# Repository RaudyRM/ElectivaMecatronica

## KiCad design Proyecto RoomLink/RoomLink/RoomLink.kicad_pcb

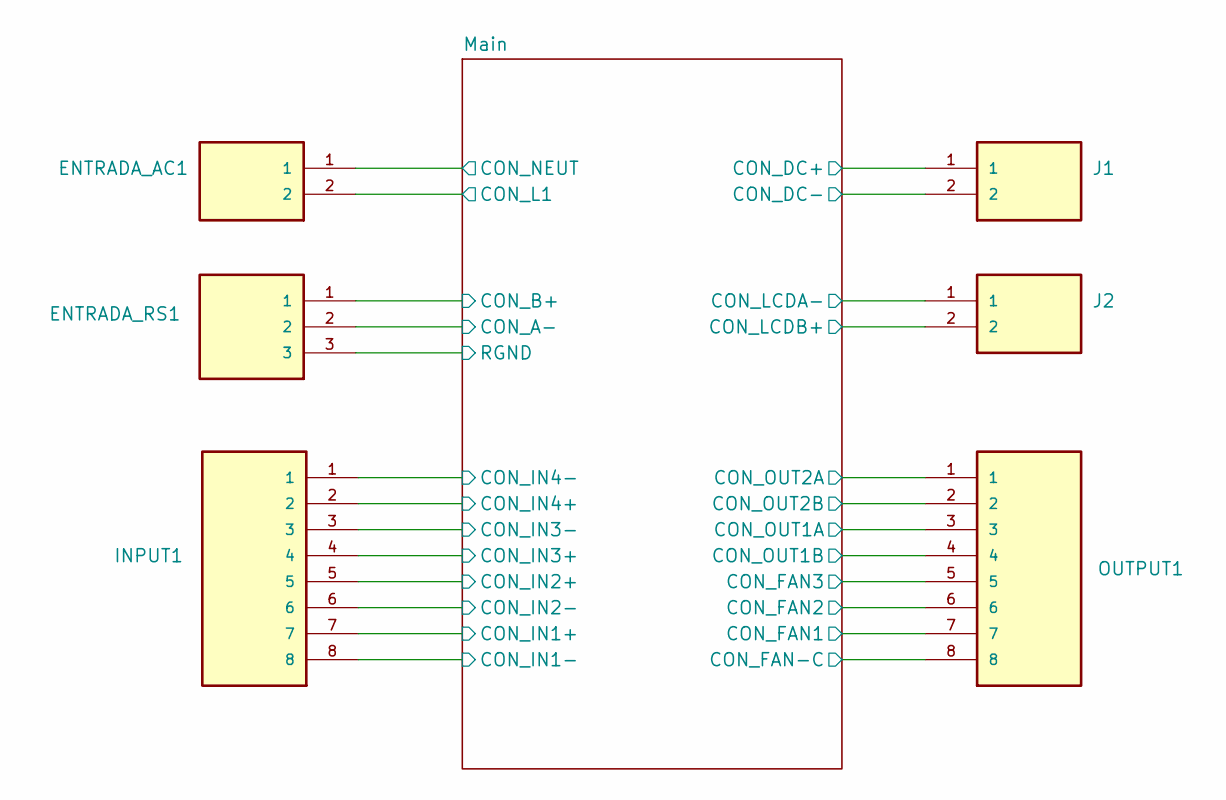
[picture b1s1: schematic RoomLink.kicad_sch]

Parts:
ENTRADA_AC1: TBP03R1-350-02BE; CUI_TBP03R1-350-02BE; PARTREV 1.0
ENTRADA_RS1: TBP03R1-350-03BE; CUI_TBP03R1-350-03BE; PARTREV 1.0
INPUT1: TBP03R1-350-08BE; CUI_TBP03R1-350-08BE; PARTREV 1.0
J1, J2: TBP03R1-350-02BE; CUI_TBP03R1-350-02BE; PARTREV 1.0
OUTPUT1: TBP03R1-350-08BE; CUI_TBP03R1-350-08BE; PARTREV 1.0

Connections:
+12V: J1.1; also elsewhere on the board
/Main/CON_A-: ENTRADA_RS1.2; also elsewhere on the board
/Main/CON_B+: ENTRADA_RS1.1; also elsewhere on the board
/Main/CON_FAN1: OUTPUT1.7; also elsewhere on the board
/Main/CON_FAN2: OUTPUT1.6; also elsewhere on the board
/Main/CON_FAN3: OUTPUT1.5; also elsewhere on the board
/Main/CON_FAN-C: OUTPUT1.8; also elsewhere on the board
/Main/CON_IN1+: INPUT1.7; also elsewhere on the board
/Main/CON_IN1-: INPUT1.8; also elsewhere on the board
/Main/CON_IN2+: INPUT1.5; also elsewhere on the board
/Main/CON_IN2-: INPUT1.6; also elsewhere on the board
/Main/CON_IN3+: INPUT1.4; also elsewhere on the board
/Main/CON_IN3-: INPUT1.3; also elsewhere on the board
/Main/CON_IN4+: INPUT1.2; also elsewhere on the board
/Main/CON_IN4-: INPUT1.1; also elsewhere on the board
/Main/CON_L1: ENTRADA_AC1.2; also elsewhere on the board
/Main/CON_LCDA-: J2.1; also elsewhere on the board
/Main/CON_LCDB+: J2.2; also elsewhere on the board
/Main/CON_NEUT: ENTRADA_AC1.1; also elsewhere on the board
/Main/CON_OUT1A: OUTPUT1.3; also elsewhere on the board
/Main/CON_OUT1B: OUTPUT1.4; also elsewhere on the board
/Main/CON_OUT2A: OUTPUT1.1; also elsewhere on the board
/Main/CON_OUT2B: OUTPUT1.2; also elsewhere on the board
/Main/RGND: ENTRADA_RS1.3; also elsewhere on the board
Earth: J1.2; also elsewhere on the board

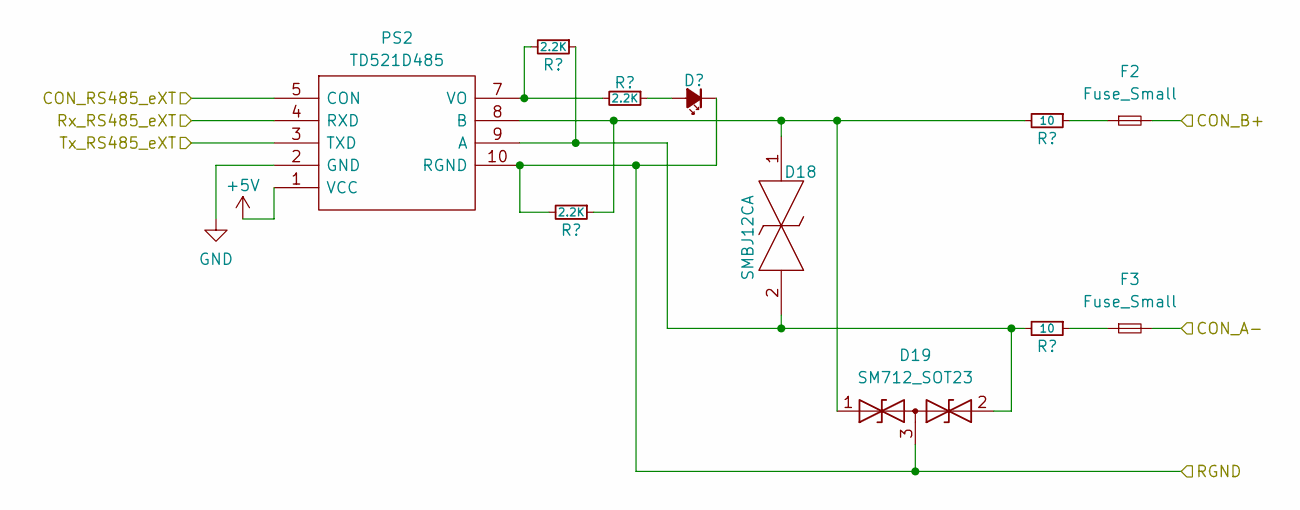
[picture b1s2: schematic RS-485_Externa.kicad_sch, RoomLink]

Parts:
D17: LED_Small_Filled; LED_0805_2012Metric_Pad1.15x1.40mm_HandSolder
D18: SMBJ12CA; DIONM5436X261N; Mouser Part Number 576-SMBJ12CA
D19: SM712_SOT23; SOT-23
F2, F3: Fuse_Small; PTS120660V010
PS2: TD521D485; Manufacturer_Part_Number TD521D485
R36, R37, R38: 2.2K; R_0805_2012Metric_Pad1.20x1.40mm_HandSolder
R39, R40: 10; R_0805_2012Metric_Pad1.20x1.40mm_HandSolder

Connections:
+5V: PS2.1 (VCC)
/Main/CON_A-: F3.2; also elsewhere on the board
/Main/CON_B+: F2.2; also elsewhere on the board
/Main/Control/CON_RS485_eXT: PS2.5 (CON); also elsewhere on the board
/Main/Control/Rx_RS485_eXT: PS2.4 (RXD); also elsewhere on the board
/Main/Control/Tx_RS485_eXT: PS2.3 (TXD); also elsewhere on the board
/Main/RGND: D17.1 (K), D19.3 (common), PS2.10 (RGND), R37.2; also elsewhere on the board
GND: PS2.2 (GND); also elsewhere on the board
unnamed: D17.2 (A), R38.1
unnamed: D18.1, D19.1 (A1), PS2.8 (B), R37.1, R39.2
unnamed: D18.2, D19.2 (A2), PS2.9 (A), R36.1, R40.2
unnamed: F2.1, R39.1
unnamed: F3.1, R40.1
unnamed: PS2.7 (VO), R36.2, R38.2

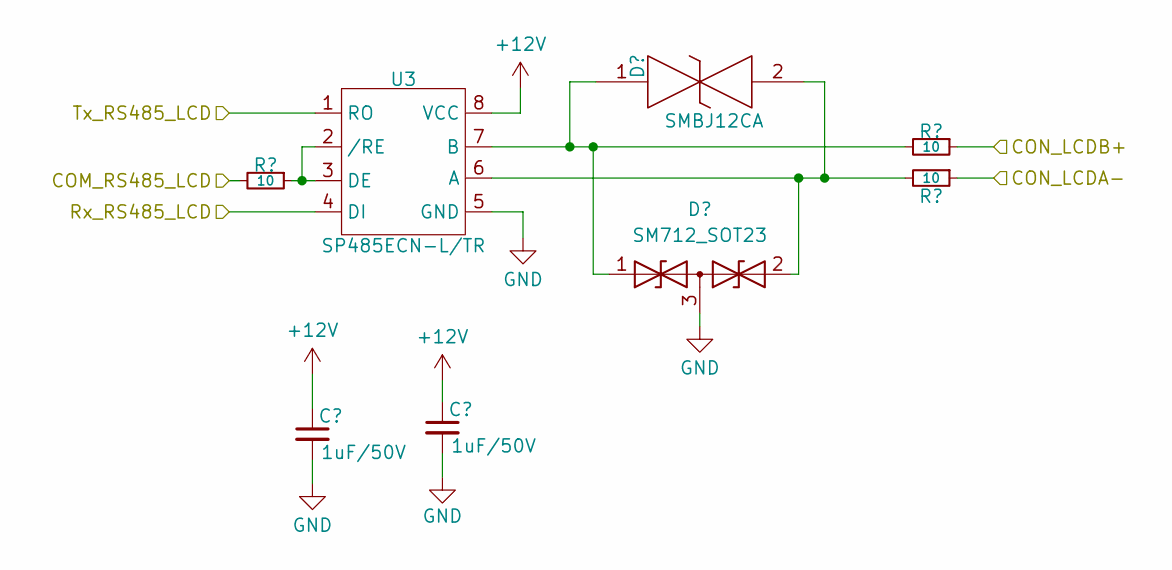
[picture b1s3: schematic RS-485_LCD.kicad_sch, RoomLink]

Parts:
C4, C5: 1uF/50V; C_0805_2012Metric; PartNo C0805C104K5RAC7411
D2: SMBJ12CA; DIONM5436X261N; Mouser Part Number 576-SMBJ12CA
D3: SM712_SOT23; SOT-23
R8, R9, R10: 10; R_0805_2012Metric_Pad1.20x1.40mm_HandSolder
U3: SP485ECN-L/TR; SP485ECN-LTR

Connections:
+12V: C4.1, C5.1, U3.8 (VCC); also elsewhere on the board
/Main/CON_LCDA-: R10.1; also elsewhere on the board
/Main/CON_LCDB+: R9.1; also elsewhere on the board
/Main/Control/COM_RS485_LCD: R8.2; also elsewhere on the board
/Main/Control/Rx_RS485_LCD: U3.4 (DI); also elsewhere on the board
/Main/Control/Tx_RS485_LCD: U3.1 (RO); also elsewhere on the board
GND: C4.2, C5.2, D3.3 (common), U3.5 (GND); also elsewhere on the board
unnamed: D2.1, D3.1 (A1), R9.2, U3.7 (B)
unnamed: D2.2, D3.2 (A2), R10.2, U3.6 (A)
unnamed: R8.1, U3.2 (/RE), U3.3 (DE)

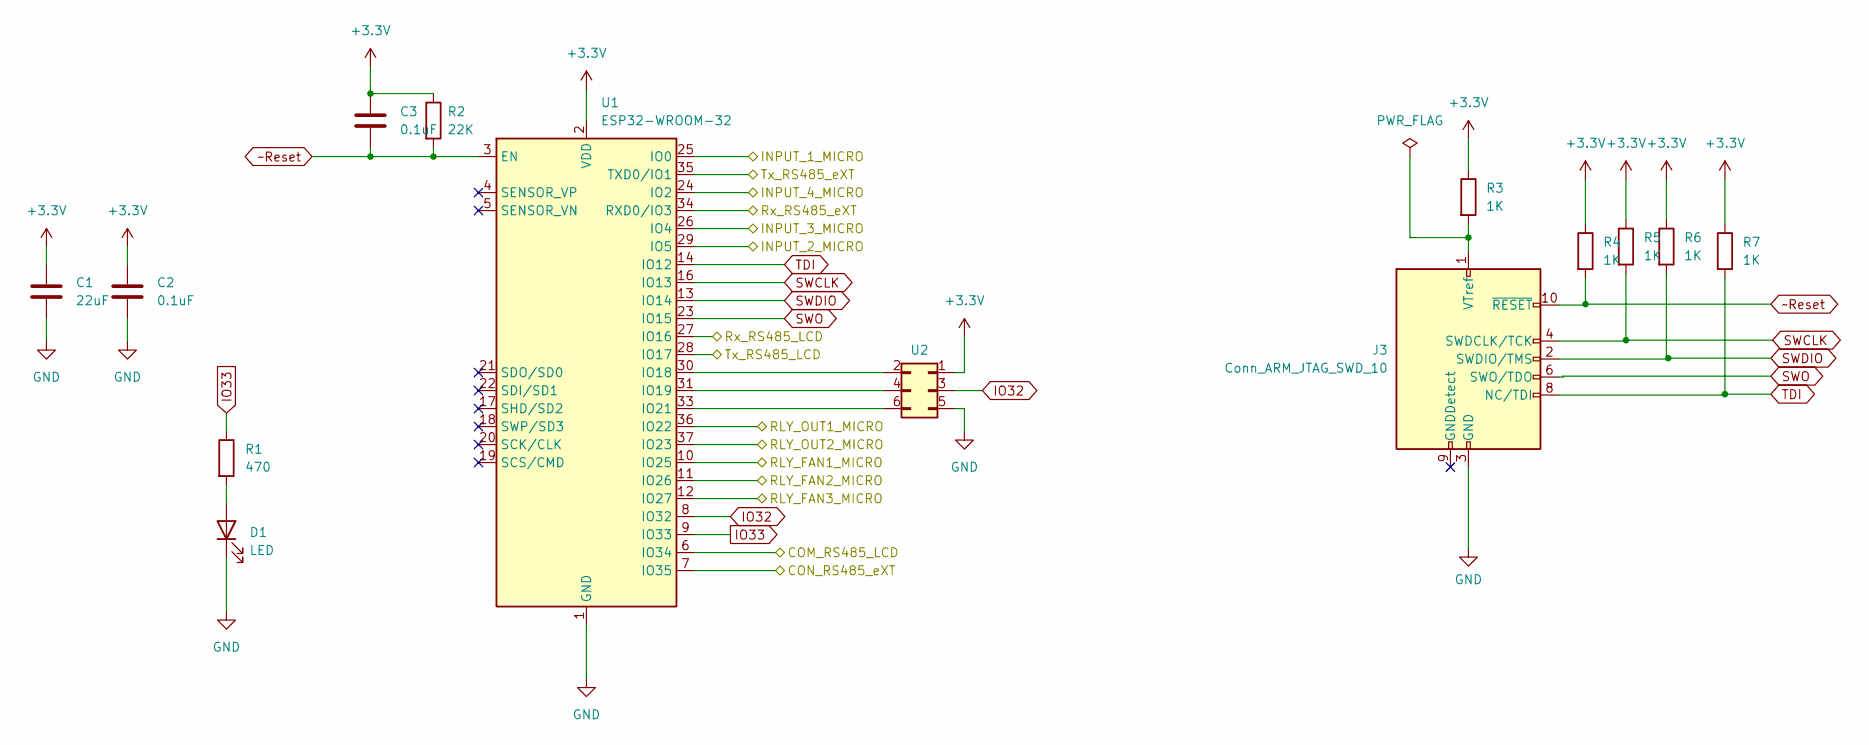
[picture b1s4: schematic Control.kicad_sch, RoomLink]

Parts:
C1: 22uF; C_0805_2012Metric
C2, C3: 0.1uF; C_0805_2012Metric
D1: LED; LED_0805_2012Metric
J3: Conn_ARM_JTAG_SWD_10; PinHeader_2x05_P1.27mm_Vertical
R1: 470; R_0805_2012Metric
R2: 22K; R_0805_2012Metric
R3, R4, R5, R6, R7: 1K; R_0805_2012Metric
U1: ESP32-WROOM-32; ESP32WROOM32EN4
U2: PinHeader2x3

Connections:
+3.3V: C1.1, C2.1, C3.1, R2.1, R3.1, R4.1, R5.1, R6.1, R7.1, U1.2 (VDD), U2.1; also elsewhere on the board
/Main/Control/COM_RS485_LCD: U1.6 (IO34); also elsewhere on the board
/Main/Control/CON_RS485_eXT: U1.7 (IO35); also elsewhere on the board
/Main/Control/INPUT_1_MICRO: U1.25 (IO0); also elsewhere on the board
/Main/Control/INPUT_2_MICRO: U1.29 (IO5); also elsewhere on the board
/Main/Control/INPUT_3_MICRO: U1.26 (IO4); also elsewhere on the board
/Main/Control/INPUT_4_MICRO: U1.24 (IO2); also elsewhere on the board
/Main/Control/RLY_FAN1_MICRO: U1.10 (IO25); also elsewhere on the board
/Main/Control/RLY_FAN2_MICRO: U1.11 (IO26); also elsewhere on the board
/Main/Control/RLY_FAN3_MICRO: U1.12 (IO27); also elsewhere on the board
/Main/Control/RLY_OUT1_MICRO: U1.36 (IO22); also elsewhere on the board
/Main/Control/RLY_OUT2_MICRO: U1.37 (IO23); also elsewhere on the board
/Main/Control/Rx_RS485_LCD: U1.27 (IO16); also elsewhere on the board
/Main/Control/Rx_RS485_eXT: U1.34 (RXD0/IO3); also elsewhere on the board
/Main/Control/Tx_RS485_LCD: U1.28 (IO17); also elsewhere on the board
/Main/Control/Tx_RS485_eXT: U1.35 (TXD0/IO1); also elsewhere on the board
GND: C1.2, C2.2, D1.1 (K), J3.3 (GND), J3.5 (GND), U1.1 (GND), U1.15 (GND), U1.38 (GND), U1.39 (GND), U2.5; also elsewhere on the board
IO32: U1.8 (IO32), U2.3
IO33: R1.1, U1.9 (IO33)
unnamed: D1.2 (A), R1.2
unnamed: J3.1 (VTref), R3.2
unnamed: U1.30 (IO18), U2.2
unnamed: U1.31 (IO19), U2.4
unnamed: U1.33 (IO21), U2.6
SWCLK: J3.4 (SWDCLK/TCK), R5.2, U1.16 (IO13)
SWDIO: J3.2 (SWDIO/TMS), R6.2, U1.13 (IO14)
SWO: J3.6 (SWO/TDO), U1.23 (IO15)
TDI: J3.8 (NC/TDI), R7.2, U1.14 (IO12)
~Reset: C3.2, J3.10 (~RESET), R2.2, R4.2, U1.3 (EN)

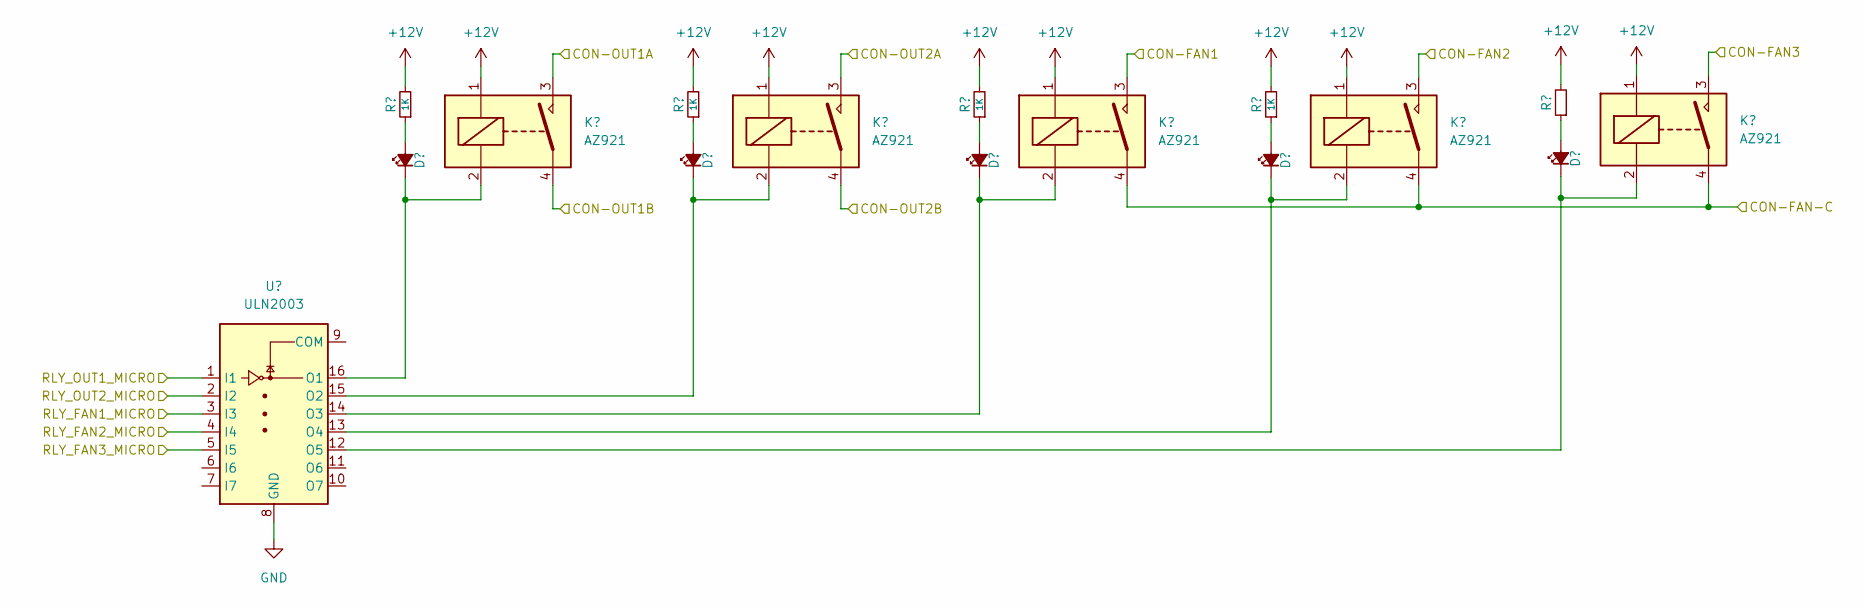
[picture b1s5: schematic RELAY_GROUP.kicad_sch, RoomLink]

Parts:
D4, D5, D6, D7, D8: LED_Small_Filled; LED_0805_2012Metric_Pad1.15x1.40mm_HandSolder
K1, K2, K3, K4, K5: AZ921
R11, R12, R13, R14, R15: 1K; R_0805_2012Metric_Pad1.20x1.40mm_HandSolder
U4: ULN2003; ULN2003-16N

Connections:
+12V: K1.1, K2.1, K3.1, K4.1, K5.1, R11.2, R12.2, R13.2, R14.2, R15.2; also elsewhere on the board
/Main/CON_FAN1: K3.3; also elsewhere on the board
/Main/CON_FAN2: K4.3; also elsewhere on the board
/Main/CON_FAN3: K5.3; also elsewhere on the board
/Main/CON_FAN-C: K3.4, K4.4, K5.4; also elsewhere on the board
/Main/CON_OUT1A: K1.3; also elsewhere on the board
/Main/CON_OUT1B: K1.4; also elsewhere on the board
/Main/CON_OUT2A: K2.3; also elsewhere on the board
/Main/CON_OUT2B: K2.4; also elsewhere on the board
/Main/Control/RLY_FAN1_MICRO: U4.3 (I3); also elsewhere on the board
/Main/Control/RLY_FAN2_MICRO: U4.4 (I4); also elsewhere on the board
/Main/Control/RLY_FAN3_MICRO: U4.5 (I5); also elsewhere on the board
/Main/Control/RLY_OUT1_MICRO: U4.1 (I1); also elsewhere on the board
/Main/Control/RLY_OUT2_MICRO: U4.2 (I2); also elsewhere on the board
GND: U4.8 (GND); also elsewhere on the board
unnamed: D4.2 (A), R11.1
unnamed: D4.1 (K), K1.2, U4.16 (O1)
unnamed: D5.2 (A), R12.1
unnamed: D5.1 (K), K2.2, U4.15 (O2)
unnamed: D6.2 (A), R13.1
unnamed: D6.1 (K), K3.2, U4.14 (O3)
unnamed: D7.2 (A), R14.1
unnamed: D7.1 (K), K4.2, U4.13 (O4)
unnamed: D8.2 (A), R15.1
unnamed: D8.1 (K), K5.2, U4.12 (O5)

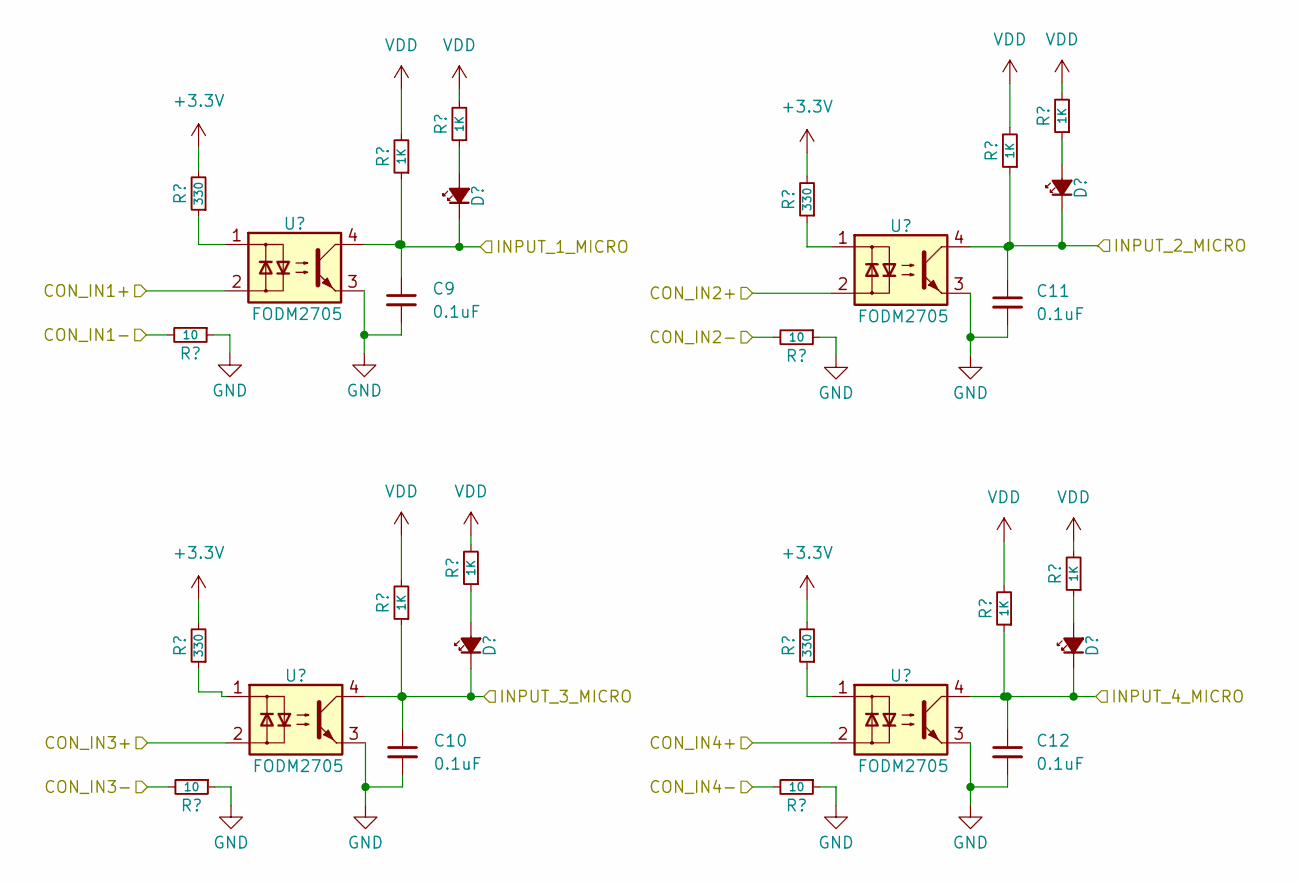
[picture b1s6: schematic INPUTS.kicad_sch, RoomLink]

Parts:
C9, C10, C11, C12: 0.1uF; C_0805_2012Metric; PartNo C0805C104K5RAC7411
D13, D14, D15, D16: LED_Small_Filled; LED_0805_2012Metric_Pad1.15x1.40mm_HandSolder
R20, R21, R28, R29: 10; R_0805_2012Metric_Pad1.20x1.40mm_HandSolder
R22, R23, R30, R31: 330; R_0805_2012Metric_Pad1.20x1.40mm_HandSolder
R24, R25, R26, R27, R32, R33, R34, R35: 1K; R_0805_2012Metric_Pad1.20x1.40mm_HandSolder
U6, U7, U8, U9: FODM2705; FODM2705-4N

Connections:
+3.3V: R22.2, R23.2, R30.2, R31.2; also elsewhere on the board
/Main/CON_IN1+: U6.2; also elsewhere on the board
/Main/CON_IN1-: R20.2; also elsewhere on the board
/Main/CON_IN2+: U8.2; also elsewhere on the board
/Main/CON_IN2-: R28.2; also elsewhere on the board
/Main/CON_IN3+: U7.2; also elsewhere on the board
/Main/CON_IN3-: R21.2; also elsewhere on the board
/Main/CON_IN4+: U9.2; also elsewhere on the board
/Main/CON_IN4-: R29.2; also elsewhere on the board
/Main/Control/INPUT_1_MICRO: C9.1, D13.1 (K), R24.1, U6.4; also elsewhere on the board
/Main/Control/INPUT_2_MICRO: C11.1, D15.1 (K), R33.1, U8.4; also elsewhere on the board
/Main/Control/INPUT_3_MICRO: C10.1, D14.1 (K), R25.1, U7.4; also elsewhere on the board
/Main/Control/INPUT_4_MICRO: C12.1, D16.1 (K), R32.1, U9.4; also elsewhere on the board
GND: C9.2, C10.2, C11.2, C12.2, R20.1, R21.1, R28.1, R29.1, U6.3, U7.3, U8.3, U9.3; also elsewhere on the board
unnamed: D13.2 (A), R26.1
unnamed: D14.2 (A), R27.1
unnamed: D15.2 (A), R34.1
unnamed: D16.2 (A), R35.1
unnamed: R22.1, U6.1
unnamed: R23.1, U7.1
unnamed: R30.1, U8.1
unnamed: R31.1, U9.1
VDD: R24.2, R25.2, R26.2, R27.2, R32.2, R33.2, R34.2, R35.2; also elsewhere on the board

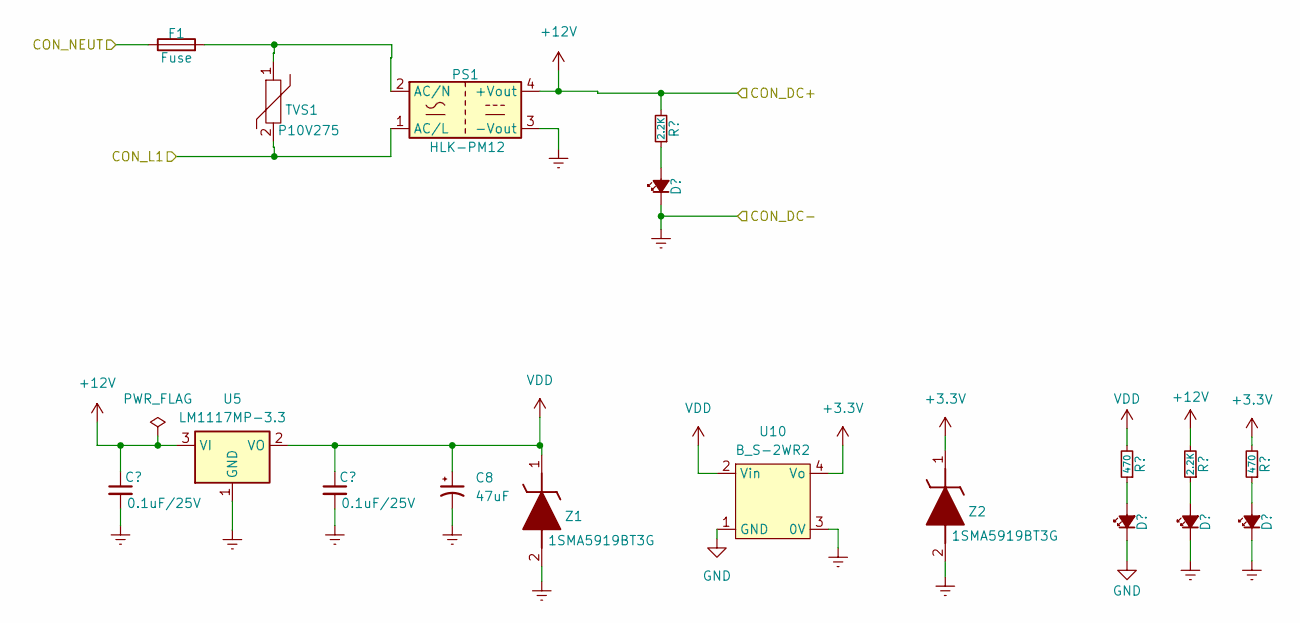
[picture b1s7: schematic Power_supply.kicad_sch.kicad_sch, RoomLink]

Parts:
C6, C7: 0.1uF/25V; C_0805_2012Metric; PartNo C0805C104K5RAC7411
C8: 47uF; CP_Elec_5x5.4
D9, D10, D11, D12: LED_Small_Filled; LED_0805_2012Metric_Pad1.15x1.40mm_HandSolder
F1: Fuse; fuse20x5
PS1: HLK-PM12; Converter_ACDC_HiLink_HLK-PMxx
R16, R18: 2.2K; R_0805_2012Metric_Pad1.20x1.40mm_HandSolder
R17, R19: 470; R_0805_2012Metric_Pad1.20x1.40mm_HandSolder
TVS1: P10V275; RV_Disc_D12mm_W6.7mm_P7.5mm
U5: LM1117MP-3.3; SOT-223-3_TabPin2
U10: B_S-2WR2
Z1, Z2: 1SMA5919BT3G; DIONM5436X261N; Mouser Part Number 863-1SMA5919BT3G

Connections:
+3.3V: R19.2, U10.4 (Vo), Z2.1 (K); also elsewhere on the board
+12V: C6.1, PS1.4 (+Vout), R16.2, R18.2, U5.3 (VI); also elsewhere on the board
/Main/CON_L1: PS1.1 (AC/L), TVS1.2; also elsewhere on the board
/Main/CON_NEUT: F1.1; also elsewhere on the board
Earth: C6.2, C7.2, C8.2, D9.1 (K), D11.1 (K), D12.1 (K), PS1.3 (-Vout), U5.1 (GND), U10.3 (0V), Z1.2 (A), Z2.2 (A); also elsewhere on the board
GND: D10.1 (K), U10.1 (GND); also elsewhere on the board
unnamed: D9.2 (A), R16.1
unnamed: D10.2 (A), R17.1
unnamed: D11.2 (A), R18.1
unnamed: D12.2 (A), R19.1
unnamed: F1.2, PS1.2 (AC/N), TVS1.1
VDD: C7.1, C8.1, R17.2, U5.2 (VO), U10.2 (Vin), Z1.1 (K); also elsewhere on the board

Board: 2 copper layers, 101 parts (0 on the bottom side), 87 nets, no tracks yet.

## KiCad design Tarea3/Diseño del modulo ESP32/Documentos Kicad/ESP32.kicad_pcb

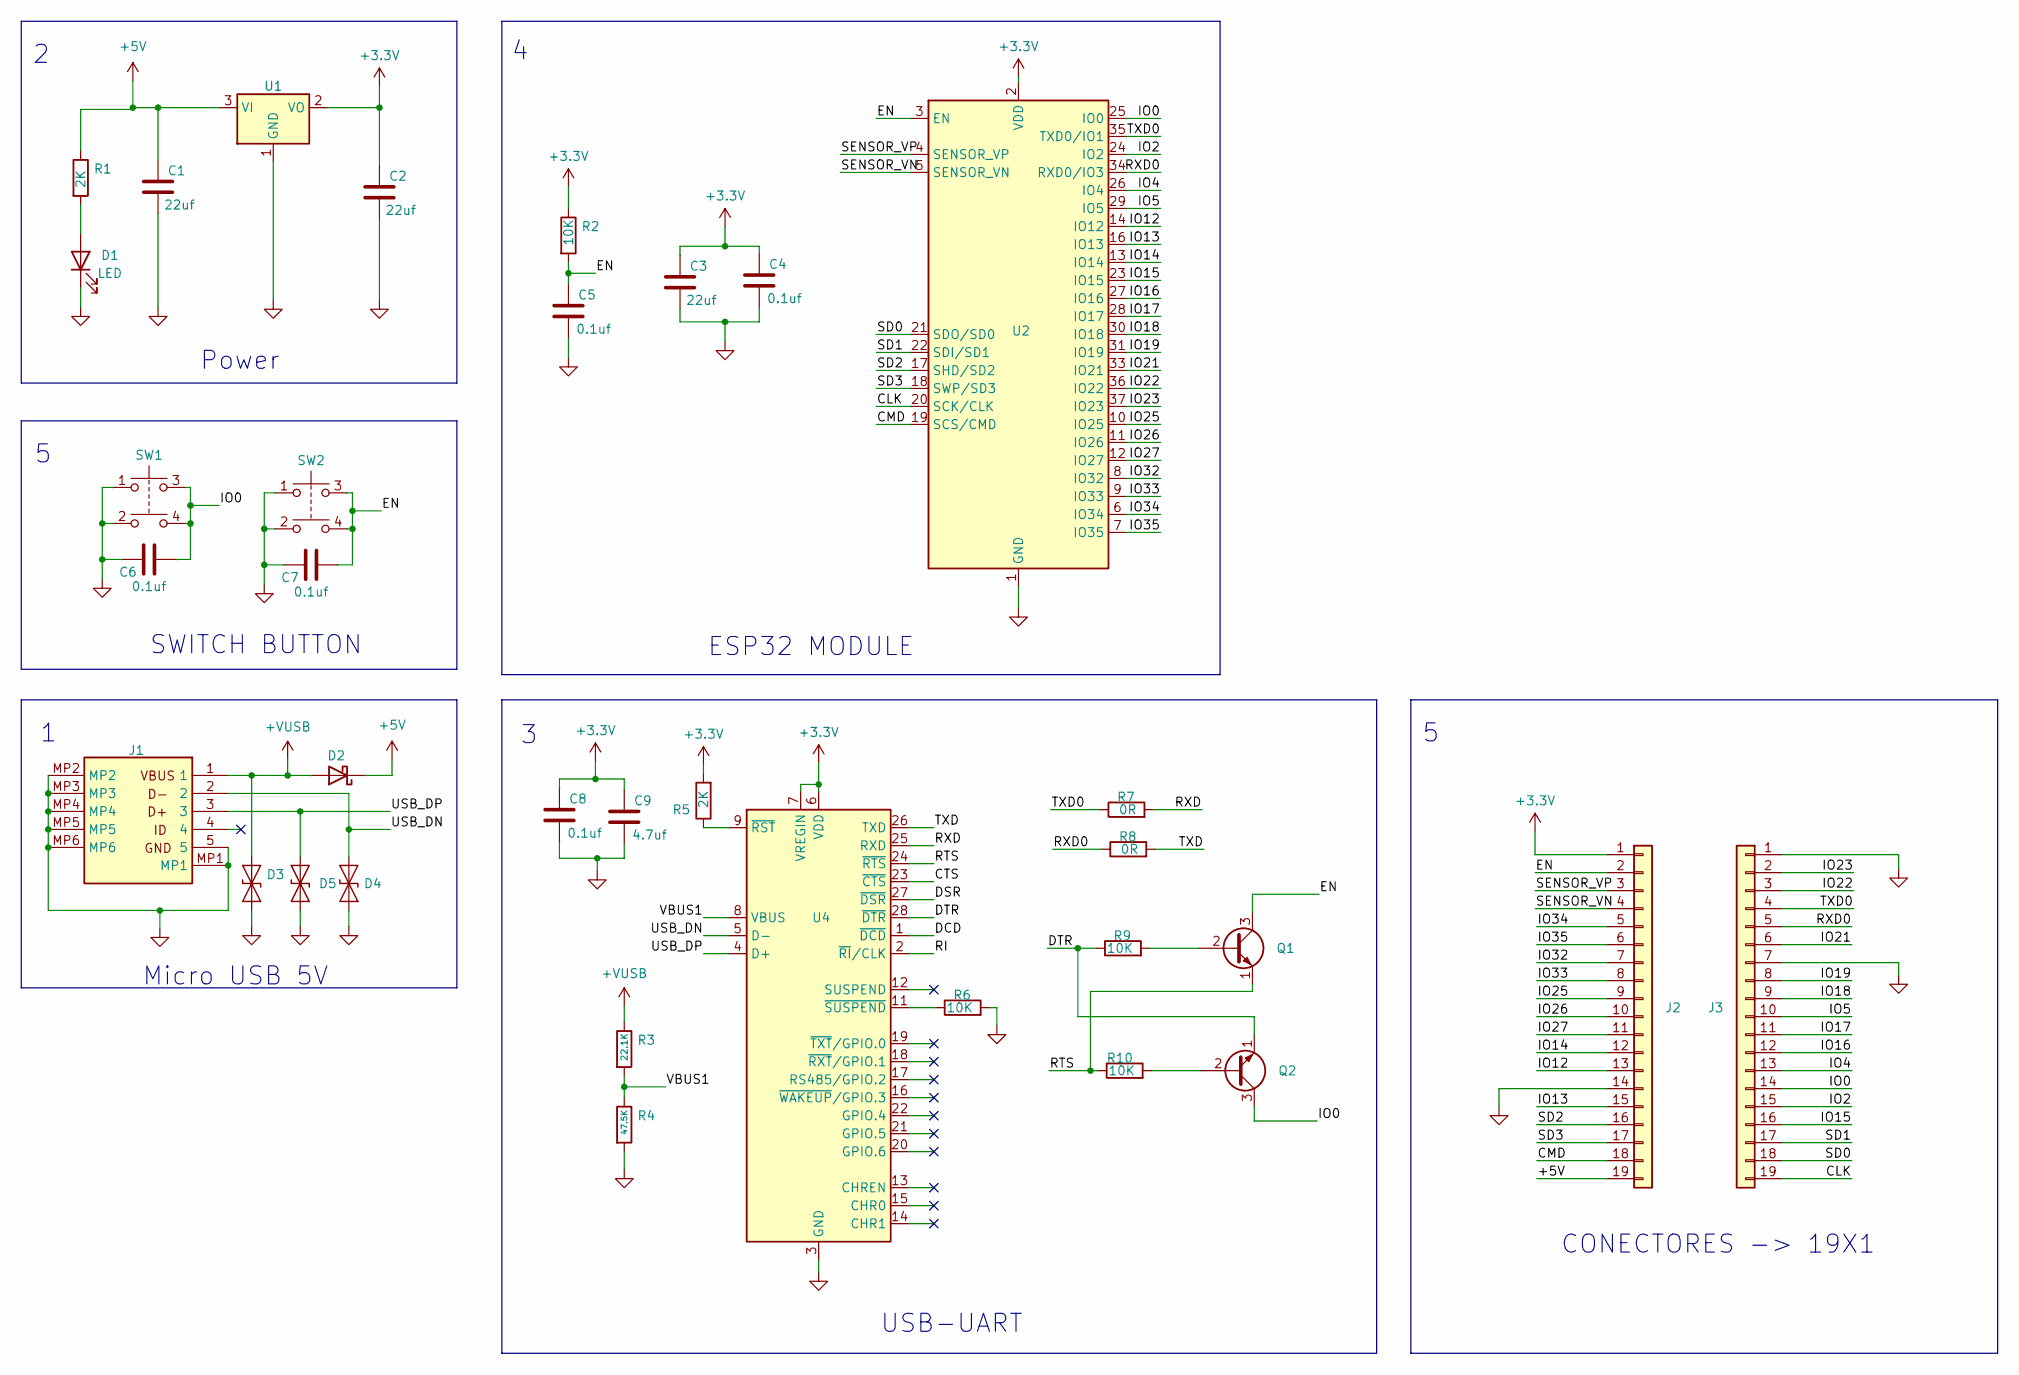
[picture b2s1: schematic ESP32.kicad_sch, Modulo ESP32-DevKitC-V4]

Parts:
C1, C2, C3: 22uf; C_0603_1608Metric_Pad1.08x0.95mm_HandSolder
C4, C5, C6, C7, C8: 0.1uf; C_0402_1005Metric_Pad0.74x0.62mm_HandSolder
C9: 4.7uf; C_0402_1005Metric_Pad0.74x0.62mm_HandSolder
D1: LED; LED_0603_1608Metric_Pad1.05x0.95mm_HandSolder
D2: D_Schottky; D_SOD-323_HandSoldering
D3, D4, D5: ESD9B3.3ST5G; D_SOD-523
J1: 10118192-0002LF; miniUSB_10118192-0002LF; Mouser Part Number 649-10118192-0002LF
J2, J3: Conn_01x19; PinHeader_1x19_P2.54mm_Vertical
Q1, Q2: S8050; SOT-23-3
R1, R5: 2K; R_0402_1005Metric_Pad0.72x0.64mm_HandSolder
R2, R6, R9, R10: 10K; R_0402_1005Metric_Pad0.72x0.64mm_HandSolder
R3: 22.1K; R_0402_1005Metric_Pad0.72x0.64mm_HandSolder
R4: 47.5K; R_0402_1005Metric_Pad0.72x0.64mm_HandSolder
R7, R8: 0R; R_0402_1005Metric_Pad0.72x0.64mm_HandSolder
SW1, SW2: SW_Push_Dual; KMT021NGJLHS
U1: AMS1117-3.3; SOT-223-3_TabPin2
U2: ESP32-WROOM-32
U4: CP2102N-Axx-xQFN28; QFN50P500X500X80-29N-D

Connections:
+3.3V: C2.1, C3.1, C4.1, C8.1, C9.1, J2.1, R2.1, R5.2, U1.2 (VO), U2.2 (VDD), U4.6 (VDD), U4.7 (VREGIN)
+5V: C1.1, D2.1 (K), J2.19, R1.1, U1.3 (VI)
+VUSB: D2.2 (A), D3.2 (A2), J1.1, R3.1
/CLK: J3.19, U2.20 (SCK/CLK)
/CMD: J2.18, U2.19 (SCS/CMD)
/CTS: U4.23 (~CTS)
/DCD: U4.1 (~DCD)
/DSR: U4.27 (~DSR)
/DTR: Q2.1 (E), R9.1, U4.28 (~DTR)
/EN: C5.1, C7.1, J2.2, Q1.3 (C), R2.2, SW2.3, SW2.4, U2.3 (EN)
/IO0: C6.1, J3.14, Q2.3 (C), SW1.3, SW1.4, U2.25 (IO0)
/IO2: J3.15, U2.24 (IO2)
/IO4: J3.13, U2.26 (IO4)
/IO5: J3.10, U2.29 (IO5)
/IO12: J2.13, U2.14 (IO12)
/IO13: J2.15, U2.16 (IO13)
/IO14: J2.12, U2.13 (IO14)
/IO15: J3.16, U2.23 (IO15)
/IO16: J3.12, U2.27 (IO16)
/IO17: J3.11, U2.28 (IO17)
/IO18: J3.9, U2.30 (IO18)
/IO19: J3.8, U2.31 (IO19)
/IO21: J3.6, U2.33 (IO21)
/IO22: J3.3, U2.36 (IO22)
/IO23: J3.2, U2.37 (IO23)
/IO25: J2.9, U2.10 (IO25)
/IO26: J2.10, U2.11 (IO26)
/IO27: J2.11, U2.12 (IO27)
/IO32: J2.7, U2.8 (IO32)
/IO33: J2.8, U2.9 (IO33)
/IO34: J2.5, U2.6 (IO34)
/IO35: J2.6, U2.7 (IO35)
/RI: U4.2 (~RI/CLK)
/RTS: Q1.1 (E), R10.1, U4.24 (~RTS)
/RXD: R7.2, U4.25 (RXD)
/RXD0: J3.5, R8.1, U2.34 (RXD0/IO3)
/SD0: J3.18, U2.21 (SDO/SD0)
/SD1: J3.17, U2.22 (SDI/SD1)
/SD2: J2.16, U2.17 (SHD/SD2)
/SD3: J2.17, U2.18 (SWP/SD3)
/SENSOR_VN: J2.4, U2.5 (SENSOR_VN)
/SENSOR_VP: J2.3, U2.4 (SENSOR_VP)
/TXD: R8.2, U4.26 (TXD)
/TXD0: J3.4, R7.1, U2.35 (TXD0/IO1)
/USB_DN: D4.2 (A2), J1.2, U4.5 (D-)
/USB_DP: D5.2 (A2), J1.3, U4.4 (D+)
/VBUS1: R3.2, R4.1, U4.8 (VBUS)
GND: C1.2, C2.2, C3.2, C4.2, C5.2, C6.2, C7.2, C8.2, C9.2, D1.1 (K), D3.1 (A1), D4.1 (A1), D5.1 (A1), J1.5, J1.MP1, J1.MP2, J1.MP3, J1.MP4, J1.MP5, J1.MP6, J2.14, J3.1, J3.7, R4.2, R6.2, SW1.1, SW1.2, SW2.1, SW2.2, U1.1 (GND), U2.1 (GND), U2.15 (GND), U2.38 (GND), U2.39 (GND), U4.3 (GND), U4.29 (GND)
unnamed: D1.2 (A), R1.2
unnamed: Q1.2 (B), R9.2
unnamed: Q2.2 (B), R10.2
unnamed: R5.1, U4.9 (~RST)
unnamed: R6.1, U4.11 (~SUSPEND)

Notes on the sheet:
ESP32 MODULE
SWITCH BUTTON
Power
Micro USB 5V
CONECTORES -> 19X1
USB-UART

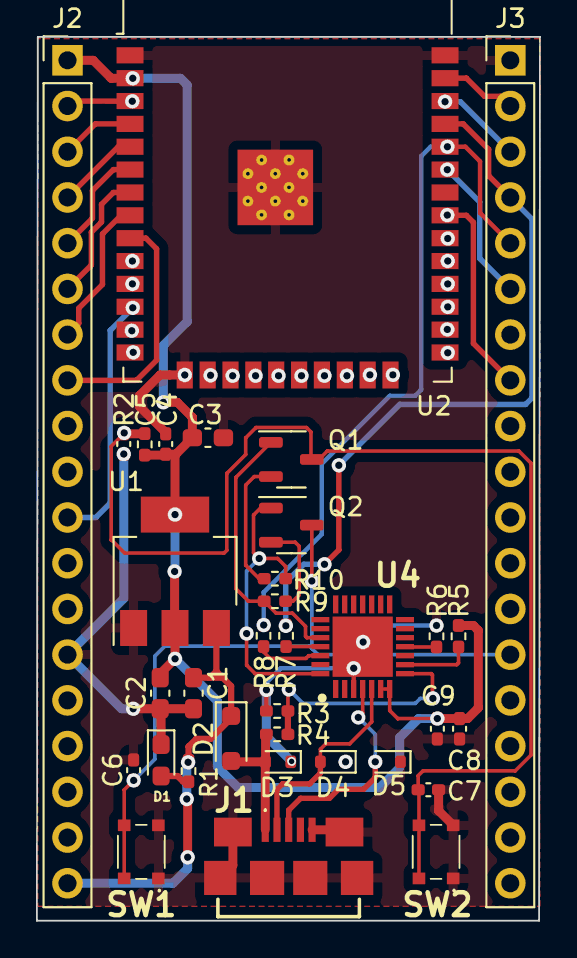
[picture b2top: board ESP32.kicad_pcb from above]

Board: 4 copper layers, 28.0 x 49.1 mm, 34 parts (0 on the bottom side), 49 nets.

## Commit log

2023-05-21 Continuacion
2023-05-25 Avance del capitulo 3
2023-05-25 Agregando una guia simple para el Git de consola
2023-05-26 Completando el 3 y sumando el 4
2023-05-26 Capitulo 4 completo
2023-05-26 Plantilla
2023-05-28 Capitulo 5
2023-06-02 Proyecto RoomLink V1.0
2023-06-05 Aprendiendo Kicad con ESP32
2023-06-09 Organizando el F.Mask
2023-06-14 Norma IEC61000
2023-06-25 RoomLink
